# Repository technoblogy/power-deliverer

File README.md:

# Power Deliverer with Current Monitor
Allows you to select one of the voltages available from a USB-C power adapter, with a continuous display of the current consumption.

For more information see: <http://www.technoblogy.com/show?441V>.

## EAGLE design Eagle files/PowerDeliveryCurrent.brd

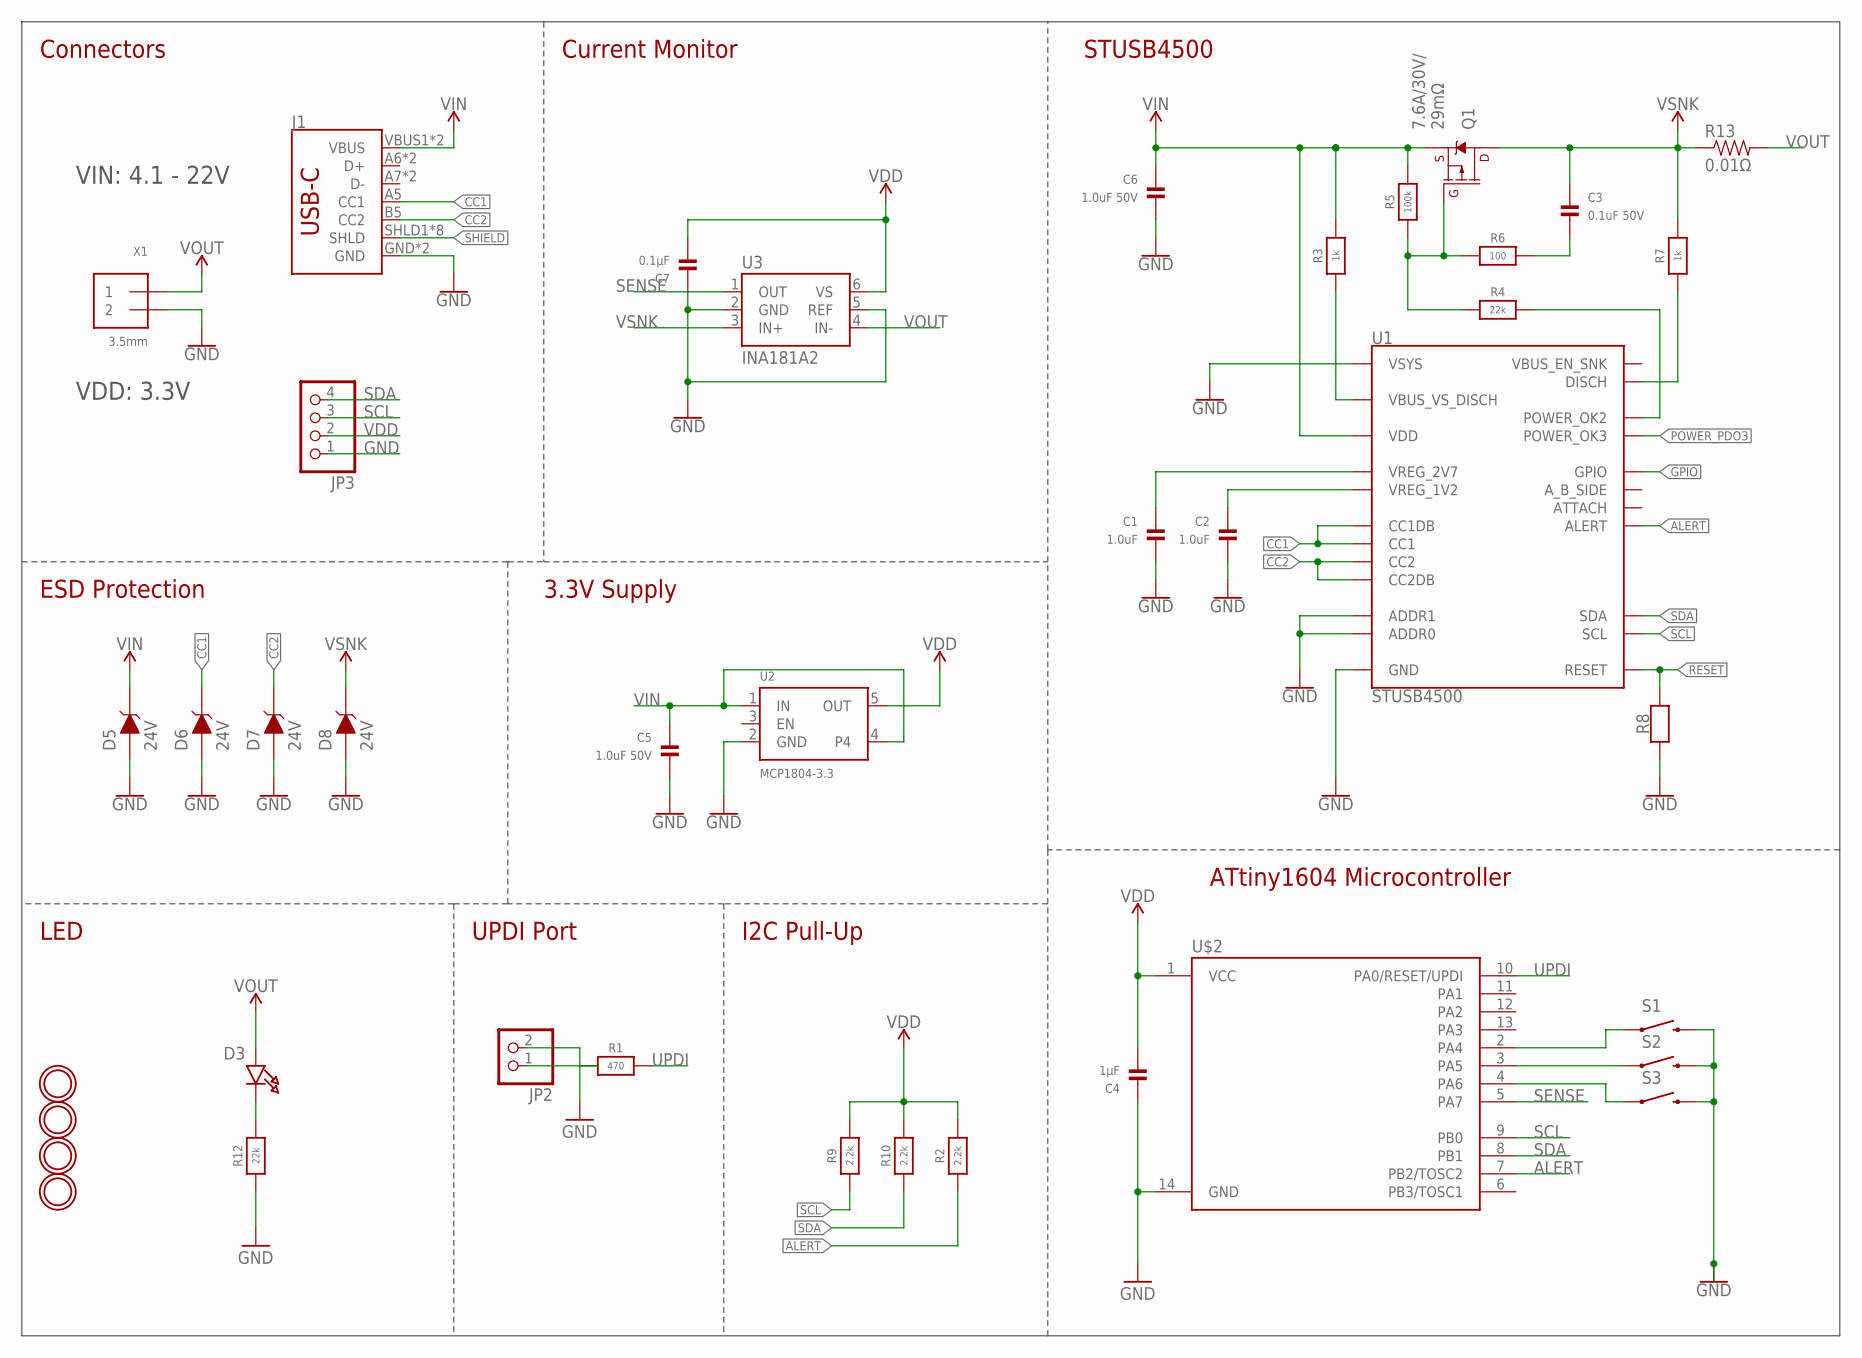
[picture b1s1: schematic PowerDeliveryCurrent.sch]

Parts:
C1, C2: 1.0uF; _0805MP
C3: 0.1uF 50V; _0805MP
C4: 1µF; _0805MP
C5, C6: 1.0uF 50V; _0805MP
C7: 0.1µF; _0805MP
D3: GREEN; CHIPLED_0805_NOOUTLINE
D5, D6, D7, D8: 24V; 0603
J1: USB_C2-LAYER; USB-C-16P
JP2: HEADER-1X2ROUND; 1X02_ROUND
JP3: HEADER-1X4ROUND; 1X04_ROUND
Q1: 9A/30V/15mΩ; 8-POWERVDFN-3X3
R1: 470; _0805MP
R2, R9, R10: 2.2k; _0805MP
R3, R7: 1k; _0805MP
R4, R12: 22k; _0805MP
R5, R8: 100k; _0805MP
R6: 100; _0805MP
R13: 0.01Ω; 1206
S1, S2, S3: SWITCH-MOMENTARY-2SMD-4.6X2.8MM; TACTILE_SWITCH_SMD_4.6X2.8MM
U1: STUSB4500; QFN-24
U2: MCP1804-3.3; SOT23-5
U3: INA181A2; SOT23-6
U$1, U$3, U$4, U$6: MOUNTINGHOLE2.5; MOUNTINGHOLE_2.5_PLATED
U$2: ATTINY414; SO14
X1: 3.5mm; TERMBLOCK_1X2-3.5MM

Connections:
1.2V: C2.1, U1.P$21 (VREG_1V2)
2.7V: C1.1, U1.P$23 (VREG_2V7)
ALERT: R2.1, U1.P$19 (ALERT), U$2.7 (PB2/TOSC2)
CC1: D6.2 (C), J1.A5 (CC1), U1.P$1 (CC1DB), U1.P$2 (CC1)
CC2: D7.2 (C), J1.B5 (CC2), U1.P$4 (CC2), U1.P$5 (CC2DB)
DISCH: R7.2, U1.P$9 (DISCH)
EN_SNK: R4.1, U1.P$20 (POWER_OK2)
GND: C1.2, C2.2, C4.1, C5.2, C6.2, C7.1, D5.1 (A), D6.1 (A), D7.1 (A), D8.1 (A), J1.GND, J1.GND2 (GND), JP2.2, JP3.1, R8.1, R12.1, S1.3 (2), S1.4 (2), S2.3 (2), S2.4 (2), S3.3 (2), S3.4 (2), U1.P$10 (GND), U1.P$12 (ADDR0), U1.P$13 (ADDR1), U1.P$22 (VSYS), U1.P$25 (GND), U2.2 (GND), U3.2 (GND), U3.5 (REF), U$2.14 (GND), X1.2
GPIO: U1.P$15 (GPIO)
unnamed: S3.1, S3.2 (1), U$2.4 (PA6)
unnamed: D3.C, R12.2
unnamed: JP2.1, R1.1
unnamed: S2.1, S2.2 (1), U$2.3 (PA5)
unnamed: S1.1, S1.2 (1), U$2.2 (PA4)
unnamed: Q1.4 (G), R4.2, R5.1, R6.1
unnamed: C3.2, R6.2
POWER_PDO3: U1.P$14 (POWER_OK3)
RESET: R8.2, U1.P$6 (RESET)
SCL: JP3.3, R9.1, U1.P$7 (SCL), U$2.9 (PB0)
SDA: JP3.4, R10.1, U1.P$8 (SDA), U$2.8 (PB1)
SENSE: U3.1 (OUT), U$2.5 (PA7)
SHIELD: J1.SHLD1 (SHLD), J1.SHLD2 (SHLD), J1.SHLD3 (SHLD), J1.SHLD4 (SHLD), J1.SHLD5 (SHLD), J1.SHLD6 (SHLD), J1.SHLD7 (SHLD), J1.SHLD8 (SHLD)
UPDI: R1.2, U$2.10 (PA0/RESET/UPDI)
VBUS_VS_DISCH: R3.1, U1.P$18 (VBUS_VS_DISCH)
VDD: C4.2, C7.2, JP3.2, R2.2, R9.2, R10.2, U2.5 (OUT), U3.6 (VS), U$2.1 (VCC)
VIN: C5.1, C6.1, D5.2 (C), J1.VBUS1 (VBUS), J1.VBUS2 (VBUS), Q1.1 (S), Q1.2 (S), Q1.3 (S), R3.2, R5.2, U1.P$24 (VDD), U2.1 (IN), U2.4
VOUT: D3.A, R13.2, U3.4 (IN-), X1.1
VSNK: C3.1, D8.2 (C), Q1.5@1 (D), Q1.5@2 (D), Q1.5@3 (D), R7.1, R13.1, U3.3 (IN+)

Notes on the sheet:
STUSB4500
Connectors
I2C Pull-Up
LED
VIN: 4.1 - 22V
7.6A/30V/ 29mΩ
ESD Protection
VDD: 3.3V
3.3V Supply
ATtiny1604 Microcontroller
UPDI Port
Current Monitor

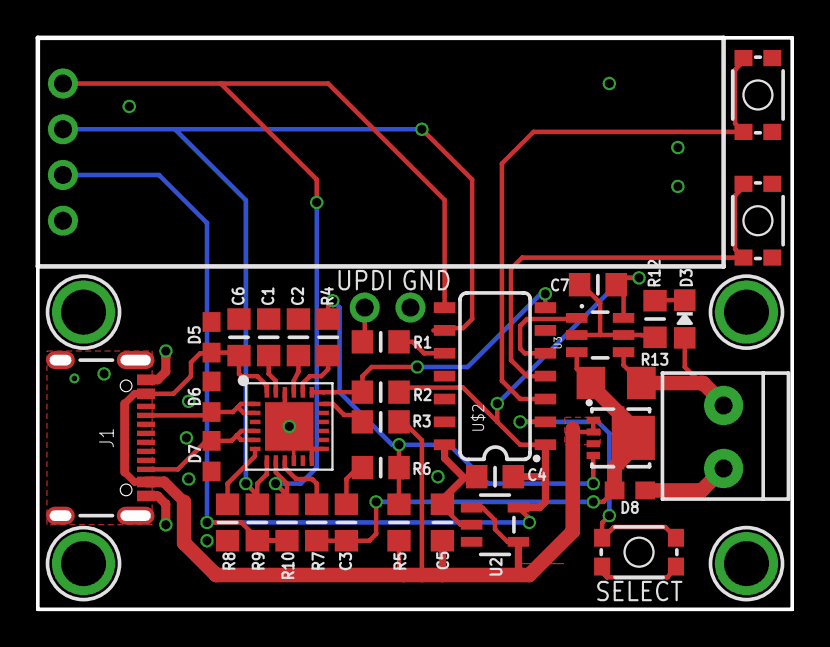
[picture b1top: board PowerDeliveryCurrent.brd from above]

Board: 2 copper layers, 41.5 x 31.4 mm, 40 parts (0 on the bottom side), 26 nets.

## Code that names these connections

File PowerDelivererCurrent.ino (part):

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// Alert interrupt **********************************************

void AlertEnable () {
  PORTB.PIN2CTRL = PORT_ISC_FALLING_gc;               // Pin change interrupt on PB2
}

void AlertDisable () {
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volatile uint8_t Cursor = 0;

void ButtonsOn () {
  // PA5 (Up), PA6 (Down), and PA4 (Select) inputs with pullups
  PORTA.PIN4CTRL = PORT_PULLUPEN_bm | PORT_ISC_FALLING_gc;
  PORTA.PIN5CTRL = PORT_PULLUPEN_bm | PORT_ISC_FALLING_gc;
  PORTA.PIN6CTRL = PORT_PULLUPEN_bm | PORT_ISC_FALLING_gc;;
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
// Main routines **********************************************

const int Sense = 3; // Arduino pin = PA7

void DisplayProfiles () {
  Scale = 1;
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
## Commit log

2022-08-23 Version 1 - 23rd August 2022
2023-02-07 Version 2 - 7th February 2023

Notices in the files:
PowerDelivererCurrent.ino:
CC BY 4.0
Licensed under a Creative Commons Attribution 4.0 International license:
http://creativecommons.org/licenses/by/4.0
parts and their libraries:
SparkFun-Connectors: Licensing: Creative Commons ShareAlike 4.0 International - https://creativecommons.org/licenses/by-sa/4.0
microbuilder: This work is placed in the public domain, and may be freely used for commercial and non-commercial work with the following conditions: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
